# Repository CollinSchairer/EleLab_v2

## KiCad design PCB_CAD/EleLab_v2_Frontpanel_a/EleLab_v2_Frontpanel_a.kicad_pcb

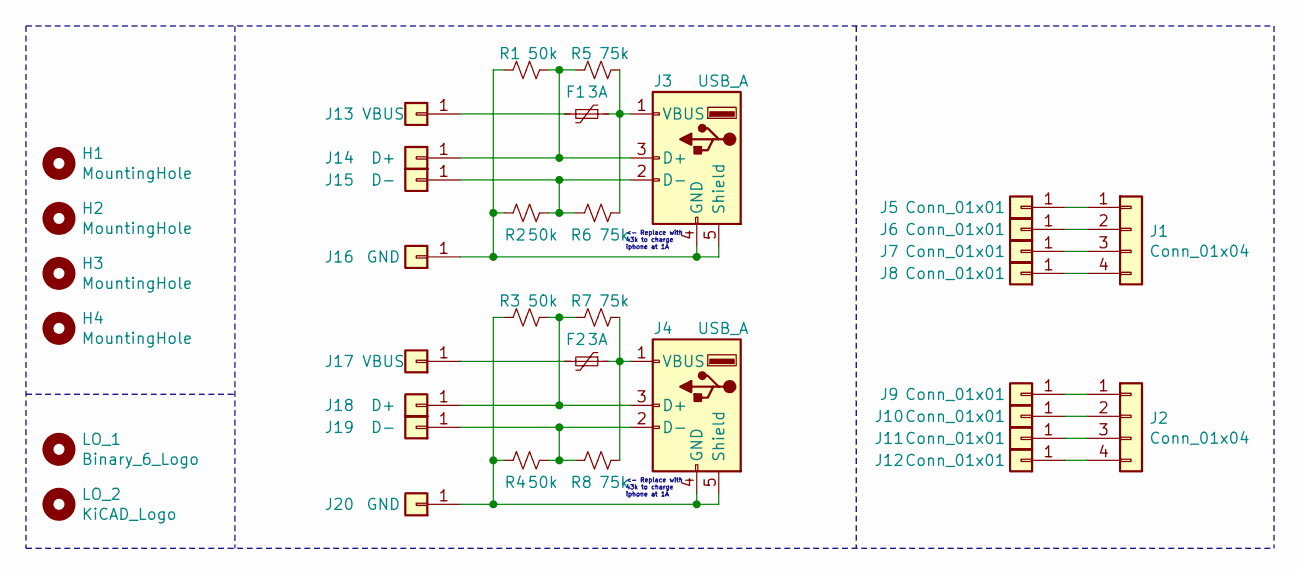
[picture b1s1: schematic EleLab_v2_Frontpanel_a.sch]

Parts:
F1, F2: 3A; Fuse_0805_2012Metric_Pad1.15x1.40mm_HandSolder
H1, H2, H3, H4: MountingHole; EigenesMountingHole_2.7mm_M2.5
J1, J2: Conn_01x04; PhoenixContact_MSTBA_2,5_4-G-5,08_1x04_P5.08mm_Horizontal
J3, J4: USB_A; USB_B_Standing
J5, J6, J7, J8, J9, J10, J11, J12: Conn_01x01; PinHeader_1x01_P2.54mm_Vertical
J13, J17: VBUS; PinHeader_1x01_P2.54mm_Vertical
J14, J18: D+; PinHeader_1x01_P2.54mm_Vertical
J15, J19: D-; PinHeader_1x01_P2.54mm_Vertical
J16, J20: GND; PinHeader_1x01_P2.54mm_Vertical
LO_1: Binary_6_Logo; Binary_6_v0.1
LO_2: KiCAD_Logo; Symbol_KiCAD-Logo_CopperAndSilkScreenTop
R1, R2, R3, R4: 50k; R_Axial_DIN0204_L3.6mm_D1.6mm_P7.62mm_Horizontal
R5, R6, R7, R8: 75k; R_Axial_DIN0204_L3.6mm_D1.6mm_P7.62mm_Horizontal

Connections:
unnamed: F1.1, J3.1 (VBUS), R5.2, R6.2
unnamed: F1.2, J13.1
unnamed: F2.1, J4.1 (VBUS), R7.2, R8.2
unnamed: F2.2, J17.1
unnamed: J1.1, J5.1
unnamed: J1.2, J6.1
unnamed: J1.3, J7.1
unnamed: J1.4, J8.1
unnamed: J2.1, J9.1
unnamed: J2.2, J10.1
unnamed: J2.3, J11.1
unnamed: J2.4, J12.1
unnamed: J3.3 (D+), J14.1, R1.2, R5.1
unnamed: J3.2 (D-), J15.1, R2.2, R6.1
unnamed: J3.4 (GND), J3.5 (Shield), J16.1, R1.1, R2.1
unnamed: J4.3 (D+), J18.1, R3.2, R7.1
unnamed: J4.2 (D-), J19.1, R4.2, R8.1
unnamed: J4.4 (GND), J4.5 (Shield), J20.1, R3.1, R4.1

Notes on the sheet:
<- Replace with 43k to charge iphone at 1A

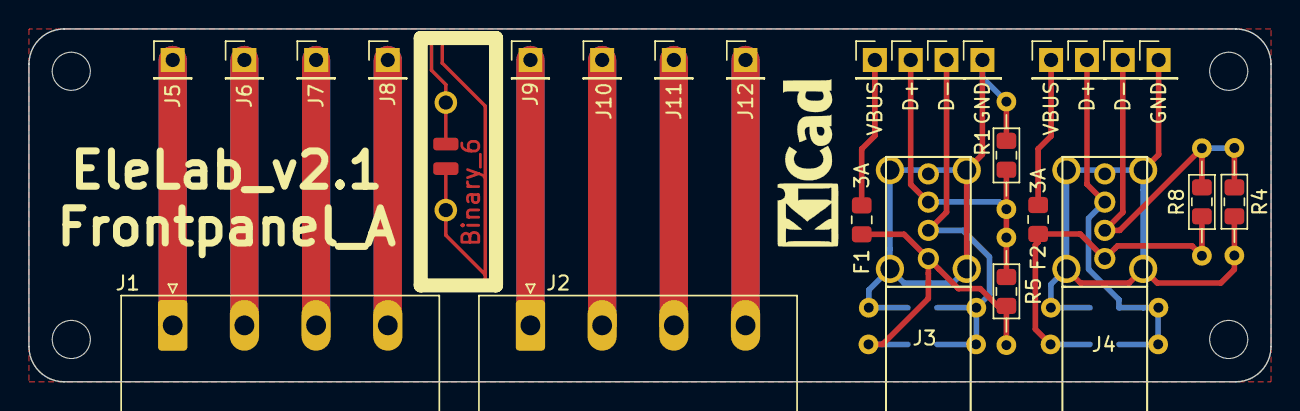
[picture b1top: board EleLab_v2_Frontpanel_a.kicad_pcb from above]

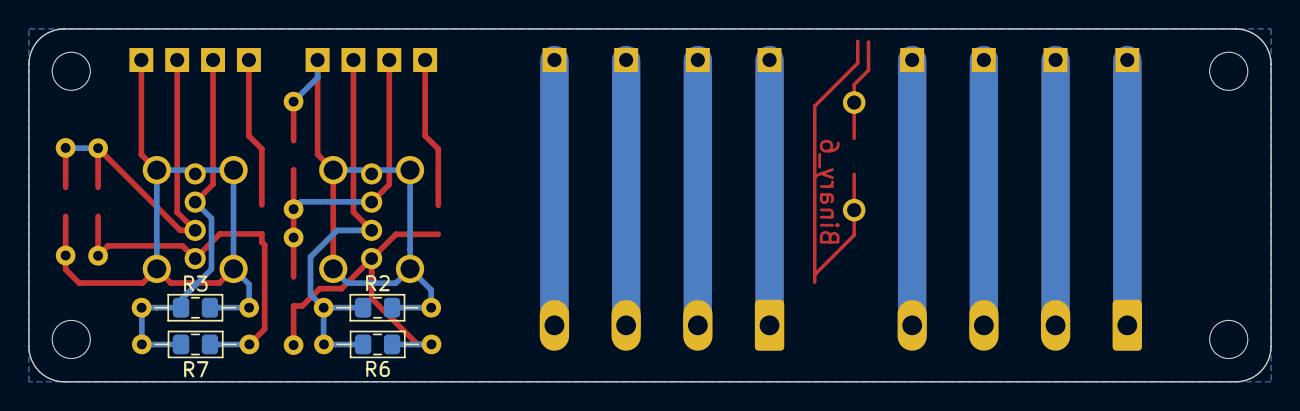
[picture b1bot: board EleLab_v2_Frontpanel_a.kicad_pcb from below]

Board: 2 copper layers, 88.0 x 25.0 mm, 36 parts (4 on the bottom side), 18 nets.

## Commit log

2020-06-17 Add files via upload
    Made STEP of all files, added more fans and vents to variable PSU, Added iOS charging support to the front panel board, created STLs for the variable power supply. Added model for USB ports.
2020-08-04 Forgot what changed, I think I finished up making STEPs of everything.
